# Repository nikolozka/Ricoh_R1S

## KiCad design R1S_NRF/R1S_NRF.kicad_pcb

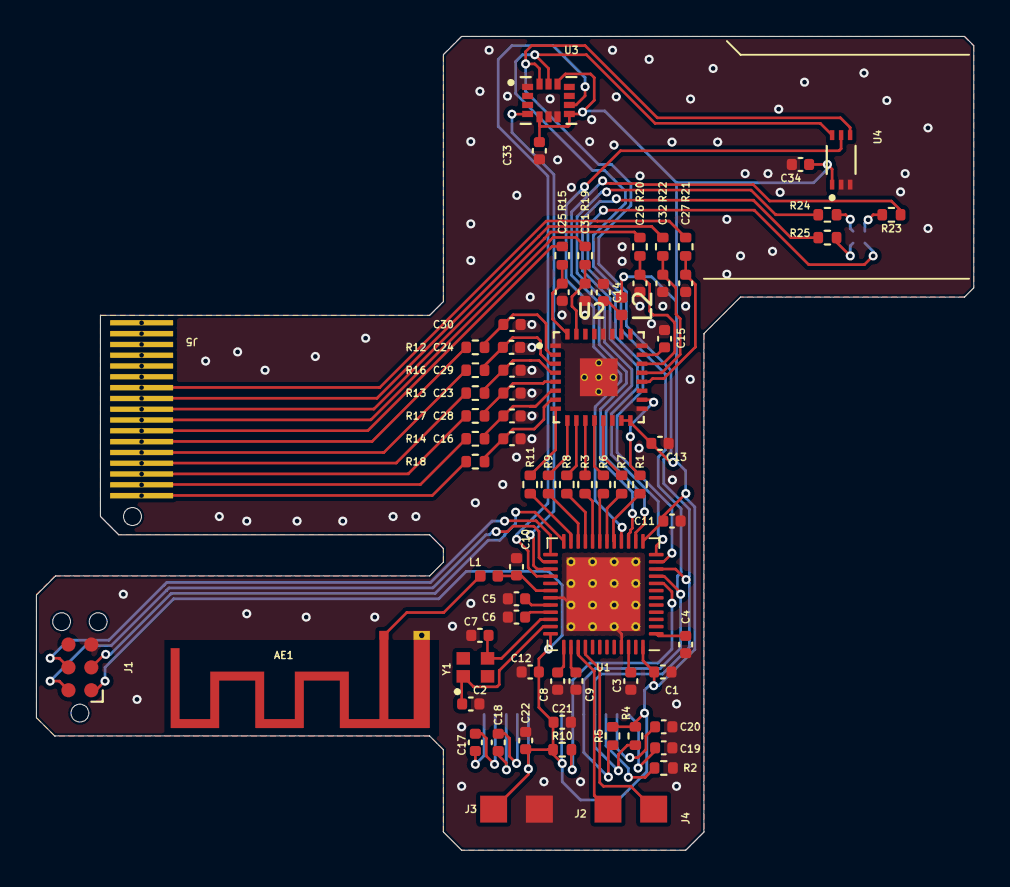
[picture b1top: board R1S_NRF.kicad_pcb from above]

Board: 2 copper layers, 52.1 x 45.2 mm, 73 parts (1 on the bottom side), 75 nets.

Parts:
AE1: Antenna_Shield; Texas_SWRA117D_2.4GHz_Right
C1, C19: 4.7uF; C_0402_1005Metric
C2, C7, C8, C9, C10: 12pF; C_0402_1005Metric
C3, C17, C18, C21, C22: 1uF; C_0402_1005Metric
C4, C11, C12, C13: 100nF; C_0402_1005Metric
C5: DNP; C_0402_1005Metric
C6: 100pF; C_0402_1005Metric
C14, C15, C16, C23, C24, C25, C26, C27, C28, C29, C30, C31, C32, C33, C34: 330nF; C_0402_1005Metric
C20: 2.2uF; C_0402_1005Metric
D1: APGF1012GBRC-07
J1: Conn_ARM_SWD_TagConnect_TC2030-NL; Tag-Connect_TC2030-IDC-NL_2x03_P1.27mm_Vertical
J2, J3: 2xPad
J4: 0.91_Display
J5: Ricoh_R1S_CN
L1: 3.9nH; L_0402_1005Metric
L2: L_Small; L_0402_1005Metric
R1, R3, R6, R7, R8, R9, R10, R11, R12, R13, R14, R15, R16, R17, R18, R19, R20, R21, R22, R23, R24, R25: 10K; R_0402_1005Metric
R2: 560K; R_0402_1005Metric
R4, R5: 4.7K; R_0402_1005Metric
U1: nRF52832-QFxx; VQFN-48-1EP_6x6mm_P0.4mm_EP4.1x4.1mm_ThermalVias
U2: ADS114S08BIRHBT; IC_ADS114S08BIRHBT
U3: LSM6DSOX; PQFN50P250X300X86-14N
U4: BH1750FVI-TR; XDCR_BH1750FVI-TR
Y1: XRCGB32M000F1H01R0; OSC_XRCGB32M000F1H01R0

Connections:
+3V3: C1.1, C11.1, C12.1, C13.2, C21.2, C22.2, C33.2, C34.2, J1.1 (VCC), J3.1, J4.5 (VCC), J4.8 (VDD), L2.1, R4.1, R5.1, R10.1, U1.13 (VDD), U1.36 (VDD), U1.48 (VDD), U2.15 (IOVDD), U2.16 (DVDD), U3.5 (VDDIO), U3.8 (VDD), U3.12 (CS), U4.1 (VCC)
/B: R25.1, U1.12 (NFC2/P0.10)
/COMM: D1.1 (COMM), U1.11 (NFC1/P0.09)
/DIN: R8.2, U1.21 (P0.18/SWO)
/DOUT: R6.2, U1.19 (P0.16)
/DVI: U1.16 (P0.13), U4.5 (DVI)
/G: R24.1, U1.14 (P0.11)
/INT1: U1.27 (P0.22), U3.4 (INT1)
/INT2: U1.28 (P0.23), U3.9 (INT2)
/R: R23.1, U1.15 (P0.12)
/RST: J1.3 (~RESET), U1.24 (P0.21/~RESET)
/S1: J2.1, U1.39 (P0.27)
/S2: J2.2, U1.40 (P0.28/AIN4)
/SCL: J4.10 (SCL), R5.2, U1.9 (P0.07), U3.13 (SCL), U4.6 (SCL)
/SCLK: R3.2, U1.20 (P0.17)
/SDA: J4.11 (SDA), R4.2, U1.10 (P0.08), U3.14 (SDA), U4.4 (SDA)
/SWDCLK: J1.4 (SWCLK), U1.25 (SWDCLK)
/SWDIO: J1.2 (SWDIO), U1.26 (SWDIO)
/S_SYNC: R11.2, U1.23 (P0.20)
/~CS: R9.2, U1.22 (P0.19)
/~DRDY: R7.2, U1.18 (P0.15)
/~RES: J4.9 (~RES), R10.2, U1.8 (P0.06)
/~RST: R1.2, U1.17 (P0.14)
GND: AE1.2 (Shield), C1.2, C2.2, C3.2, C4.2, C5.2, C6.2, C7.2, C8.1, C9.1, C10.2, C11.2, C12.2, C13.1, C14.1, C15.2, C16.1, C19.2, C20.2, C21.1, C22.1, C23.1, C24.1, C25.1, C26.1, C27.1, C28.2, C29.2, C30.2, C31.2, C32.2, C33.1, C34.1, J1.5 (GND), J3.2, J4.7 (VSS), R2.2, U1.31 (VSS), U1.45 (VSS), U1.49 (VSS), U2.1 (AINCOM), U2.14 (DGND), U2.17 (CLK), U2.24 (REFCOM), U2.27 (AVSS), U2.28 (AVSS), U2.33 (THERMAL_PAD), U3.1 (SDO/SA0), U3.6 (GND), U3.7 (GND), U4.2 (ADDR), U4.3 (GND)
unnamed: AE1.1 (A), L1.1
unnamed: C19.1, J4.14 (VCC)
unnamed: D1.4 (B), R25.2
unnamed: D1.3 (G), R24.2
unnamed: D1.2 (R), R23.2
unnamed: C18.1, J4.4 (C1N)
unnamed: C18.2, J4.3 (C1P)
unnamed: C17.1, J4.2 (C2N)
unnamed: C17.2, J4.1 (C2P)
unnamed: J4.12 (IREF), R2.1
unnamed: C20.1, J4.13 (VCOMH)
unnamed: J5.1 (LCD), R18.2
unnamed: J5.2 (LCD), R14.2
unnamed: J5.3 (LCD), R17.2
unnamed: J5.4 (LCD), R13.2
unnamed: J5.5 (LCD), R16.2
unnamed: J5.6 (LCD), R12.2
unnamed: J5.7 (LCD), R15.2
unnamed: J5.8 (LCD), R19.2
unnamed: J5.9 (LCD), R20.2
unnamed: J5.10 (LCD), R22.2
unnamed: J5.11 (LCD), R21.2
unnamed: C10.1, L1.2, U1.30 (ANT)
unnamed: C4.1, U1.1 (DEC1)
unnamed: C5.1, U1.32 (DEC2)
unnamed: C6.1, U1.33 (DEC3)
unnamed: C3.1, U1.46 (DEC4)
unnamed: C8.2, U1.37 (P0.25)
unnamed: C9.2, U1.38 (P0.26)
unnamed: C7.1, U1.34 (XC1), Y1.3
unnamed: C2.1, U1.35 (XC2), Y1.1
unnamed: C16.2, R18.1, U2.7 (AIN0)
unnamed: C28.1, R14.1, U2.6 (AIN1)
unnamed: C23.2, R17.1, U2.5 (AIN2)
unnamed: C29.1, R13.1, U2.4 (AIN3)
unnamed: C24.2, R16.1, U2.3 (AIN4)
unnamed: C30.1, R12.1, U2.2 (AIN5)
unnamed: C14.2, L2.2, U2.26 (AVDD)
unnamed: R8.1, U2.10 (DIN)
unnamed: R6.1, U2.12 (DOUT/~DRDY)
unnamed: C26.2, R20.1, U2.22 (GPIO0/AIN8)
unnamed: C32.1, R22.1, U2.21 (GPIO1/AIN9)
unnamed: C27.2, R21.1, U2.20 (GPIO2/AIN10)
unnamed: C31.1, R19.1, U2.31 (REFN1/AIN7)
unnamed: C15.1, U2.23 (REFOUT)
unnamed: C25.2, R15.1, U2.32 (REFP1/AIN6)
unnamed: R3.1, U2.11 (SCLK)
unnamed: R11.1, U2.8 (START/SYNC)
unnamed: R9.1, U2.9 (~CS)
unnamed: R7.1, U2.13 (~DRDY)
unnamed: R1.1, U2.18 (~RESET)

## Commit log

2023-10-12 back in business commit
2023-10-12 added hardware files
2023-10-18 Accelerometer is Working
2023-10-18 WIP lvgl

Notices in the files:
R1S_NRF/R1S_NRF.kicad_pcb:
https://creativecommons.org/licenses/by/4.0
License: CC BY 4.0
